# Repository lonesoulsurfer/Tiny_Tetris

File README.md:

# Tiny_Tetris

YouTube Vid
https://www.youtube.com/watch?v=bwNg85aia90&feature=youtu.be

Ever wanted a pocket sized Tetris that you could whip out anytime you wanted?  Well you are in luck.  This build usues an ATTiny85 to run Tetris on an OLED SDD1306 screen.  It's tiny but definitely usable and did I mention it's ridiculously fun to play!

You'll find all of the files in this repository to build your own

I've also done a step by step guide on Instructables in case you are new to this type of thing.  It's takes you through the build and programming the ATTiny85

Instructables - How to program an ATtiny85 & ATtiny13a
https://www.instructables.com/Tiny-Tetris-ATtiny85-Project/

Instructables - ATtiny 85/13 Programmer
https://www.instructables.com/Programmer-for-ATtiny-85/

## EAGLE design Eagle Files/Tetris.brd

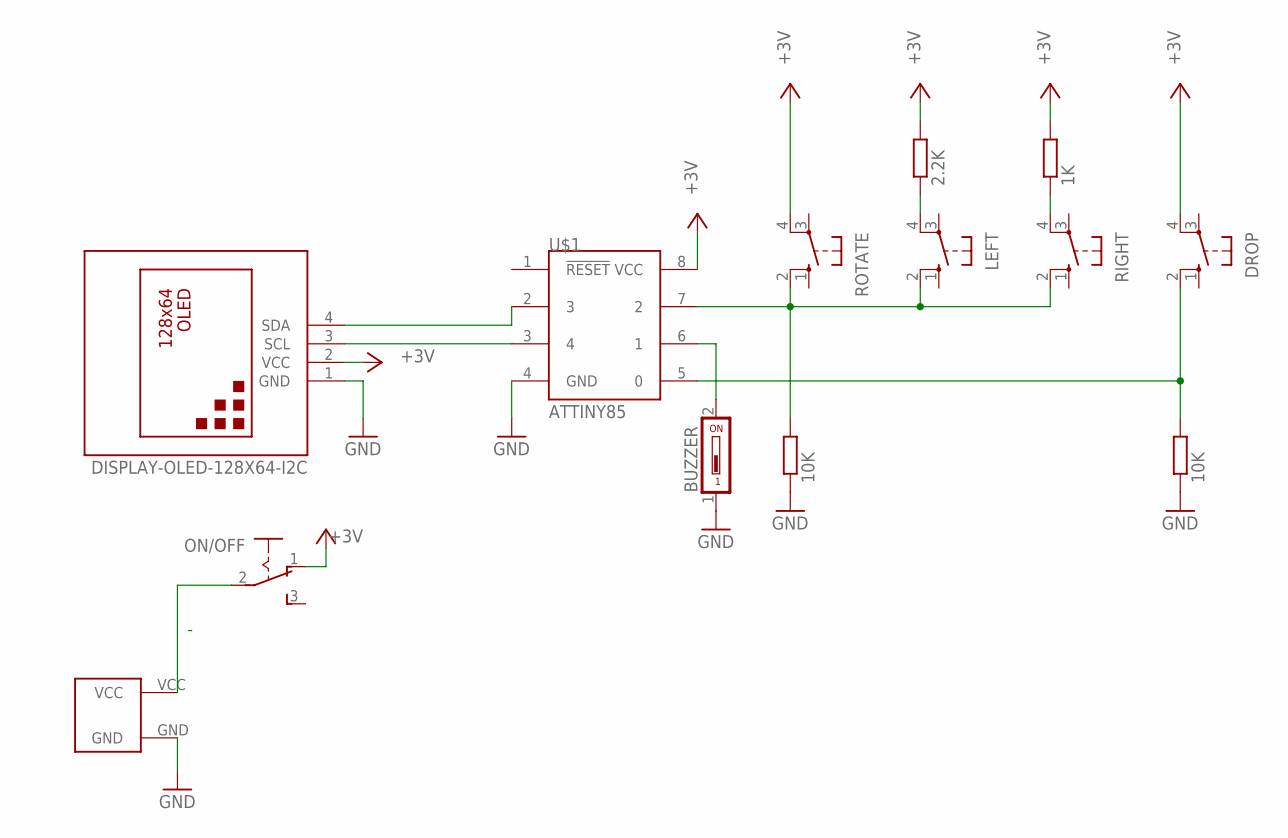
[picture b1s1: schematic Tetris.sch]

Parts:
BUZZER: DS01; DS-01
DROP: 10-XX; B3F-10XX
LEFT: 10-XX; B3F-10XX
ON/OFF: M251
R1: 2.2K; 0207/10
R2, R4: 10K; 0207/10
R3: 1K; 0207/10
RIGHT: 10-XX; B3F-10XX
ROTATE: 10-XX; B3F-10XX
U$1: ATTINY85; 8P3
U$2: DISPLAY-OLED-128X64-I2C
U$5: CR2032; CR2032-20MM

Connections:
+3V3: DROP.4 (P1), ON/OFF.1 (O), R1.2, R3.2, ROTATE.4 (P1), U$1.8 (VCC), U$2.2 (VCC)
GND: BUZZER.1, R2.1, R4.1, U$1.4 (GND), U$2.1 (GND), U$5.GND
unnamed: U$1.3 (4), U$2.3 (SCL)
unnamed: U$1.2 (3), U$2.4 (SDA)
unnamed: LEFT.4 (P1), R1.1
unnamed: DROP.2 (S1), R2.2, U$1.5 (0)
unnamed: BUZZER.2, U$1.6 (1)
unnamed: R3.1, RIGHT.4 (P1)
unnamed: LEFT.2 (S1), R4.2, RIGHT.2 (S1), ROTATE.2 (S1), U$1.7 (2)
unnamed: ON/OFF.2, U$5.VCC

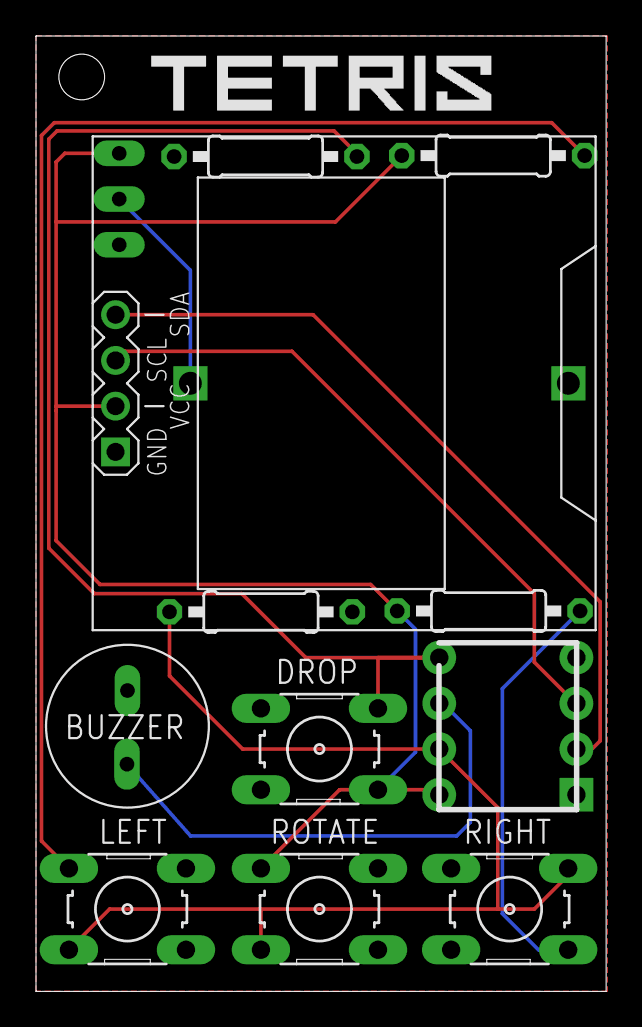
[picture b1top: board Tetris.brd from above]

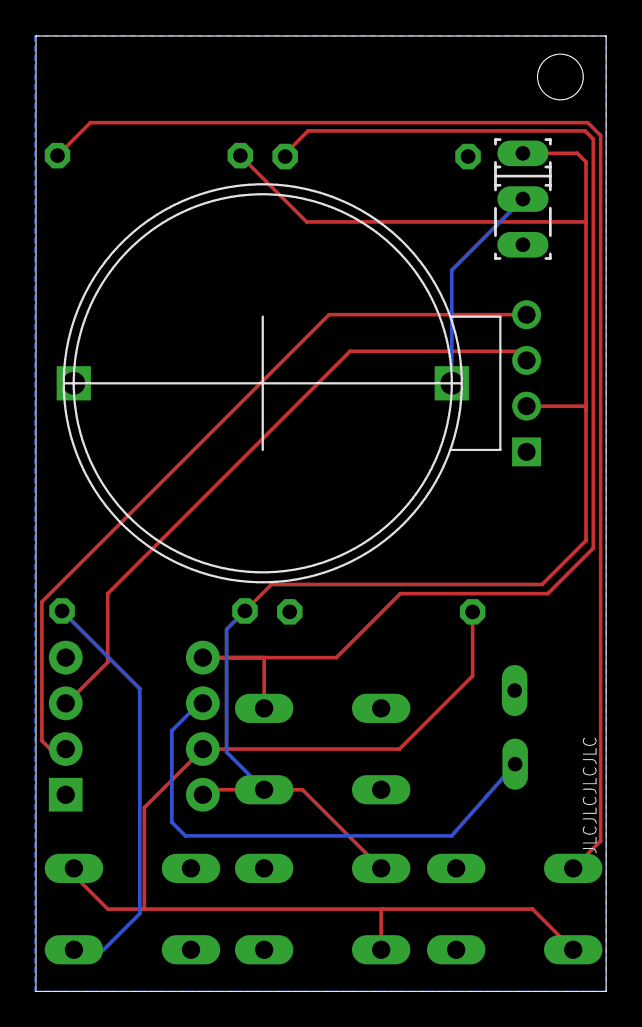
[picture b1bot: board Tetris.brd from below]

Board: 2 copper layers, 31.7 x 53.1 mm, 13 parts (2 on the bottom side), 10 nets.

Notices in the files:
parts and their libraries:
diy-modules: Released under the Creative Commons Attribution 4.0 International License: http://creativecommons.org/licenses/by/4.0
